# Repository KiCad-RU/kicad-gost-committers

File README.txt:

Build PCAD schematic importer:
# install dependencies
mkdir build
cd build
cmake -DKICAD_SCRIPTING=OFF -DKICAD_SCRIPTING_MODULES=OFF \
      -DKICAD_SCRIPTING_WXPYTHON=OFF \
      -DCMAKE_BUILD_TYPE=Debug \
      -DKICAD_SPICE=OFF \
      -DUSE_PCAD2KICAD=ON \
      -DKICAD_GOST=ON ..
make -j2 pcad2kicadsch
Run:
./extra/pcad2kicadsch/pcad2kicadsch

KiCad README
============
For specific documentation like Compiling, GUI translation, old
changelogs see the Documentation subfolder.

Files
-----
AUTHORS.txt       - The authors, contributors, document writers and translators list
CMakeList.txt     - Main CMAKE build tool script
COPYRIGHT.txt     - A copy of the GNU General Public License Version 2
CTestConfig.cmake - Support for CTest and CDash testing tools
Doxyfile          - Doxygen config file for KiCad
INSTALL.txt       - The release (binary) installation instructions
TODO.txt          - Todo list (looks outdated)
uncrustify.cfg    - Uncrustify config file for uncrustify sources formatting tool

Subdirectories
--------------
3d-viewer         - Sourcecode of the 3D viewer
bitmap2component  - Sourcecode of the bitmap to pcb artwork converter
bitmaps_png       - Menu and program icons
CMakeModules      - Modules for the CMAKE build tool
common            - Sourcecode of the common library
cvpcb             - Sourcecode of the CvPCB tool
demos             - Some demo examples
Documentation     - Developer documentation. Old changelogs etcetera.
eeschema          - Sourcecode of the schematic editor
gerbview          - Sourcecode of the gerber viewer
helpers           - Helper tools and utilities for development
include           - Interfaces to the common library
kicad             - Sourcecode of the project manager
lib_dxf           - Sourcecode of the polygon library
new               - Staging area for the new schematic library format
pagelayout_editor - Sourcecode of the pagelayout editor
patches           - Collection of patches for external dependencies
pcbnew            - Sourcecode of the printed circuit board editor
plugins           - Sourcecode of the new plugin concept
polygon           - Sourcecode of the polygon library
potrace           - Sourcecode of the potrace library
qa                - Testcases using the python interface
resources         - Resources for freedesktop mime-types for linux
scripting         - SWIG Python scripting definitions
scripts           - Helper scripts for various things
template          - Project and pagelayout templates
tools             - Other miscellaneous helpers for testing
utils             - Small utils for kicad, e.g. IDF tools

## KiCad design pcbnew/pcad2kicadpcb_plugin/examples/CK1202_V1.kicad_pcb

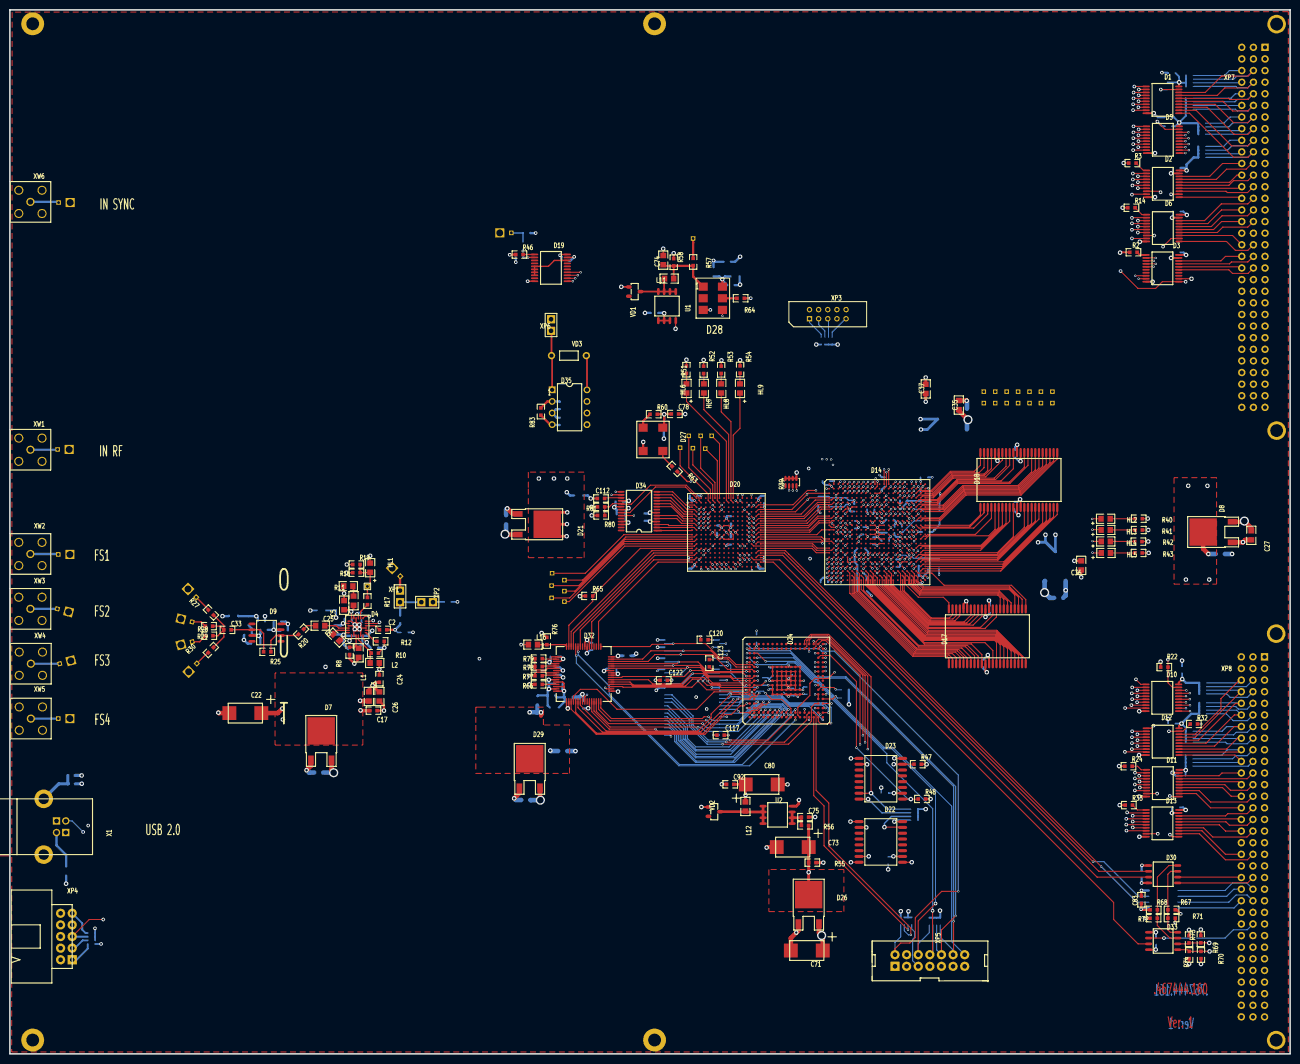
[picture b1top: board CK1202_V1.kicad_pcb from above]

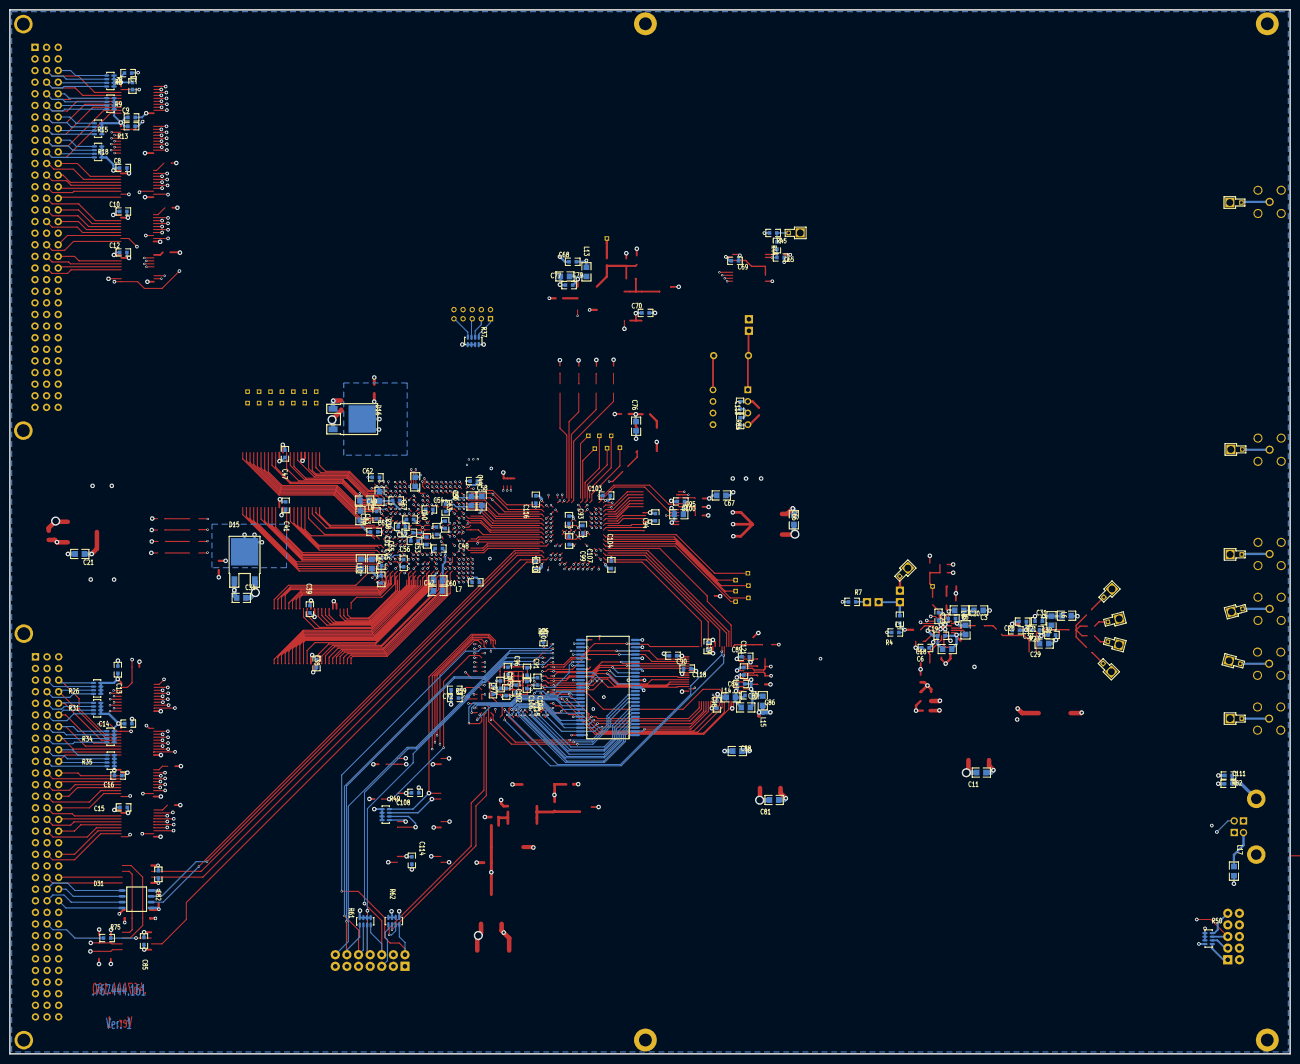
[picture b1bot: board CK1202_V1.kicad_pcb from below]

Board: 6 copper layers, 280.0 x 228.3 mm, 328 parts (151 on the bottom side), 519 nets.

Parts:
1, 2, 4, 5, 6, 7, 8, 9, 10, 11, 12, 13: YESF-085/50; CABLE_1
3: PIN40X40X24; PIN40X40X24_1
C1, C2, C28: 1000; C_SMD0603_1
C3: 0,022 мкФ; C_SMD0805_1
C4: 680; C_SMD0805_1
C5: 47; C_SMD0805_1
C6, C19, C84, C111: 0,01 мк; C_SMD0603_1
C7, C8, C9, C10, C12, C13, C14, C15, C16, C17, C20, C23, C24, C30, C32, C33, C38, C39, C40, C41, C46, C47, C48, C49, C50, C51, C52, C53, C54, C55, C56, C58, C60, C61, C62, C63, C64, C68, C69, C70, C72, C75, C78, C79, C82, C83, C85, C86, C89, C90, C91, C92, C93, C94, C96, C97, C98, C99, C100, C101, C102, C103, C104, C105, C106, C107, C108, C109, C110, C112, C113, C114, C115, C116, C117, C118, C119, C120, C121, C122, C123: 0,1 мк; C_SMD0603_1
C11, C18, C21, C26, C27, C29, C31, C34, C35, C36, C37, C42, C43, C44, C45, C57, C59, C66, C67, C74, C76, C77, C81, C87, C88, C95: 10 мк; C_SMD0805_1
C22, C71, C73, C80: 100; C+7343_1
C25: 100; C_SMD0805_1
C65: 220; C_SMD0603_1
D1, D2, D3, D5, D6, D10, D11, D12, D13, D19: SN74AC245DB; 74AC245_1
D4: ADF4360-8BCP; ADF4360_1
D7, D8, D26: LM1117DTX-3,3; LM1117_1
D9: AD8009AR; AD8009_1
D14: EP2C20F484C7; EP2C20F484_1
D15, D21: LM1117DTX-3,3; LM1117-ADJ_1
D16: LM1117DTX-ADJ; LM1117-ADJ_1
D17, D18: IS61LV51216; IS61LV51216_1_1
D20: EPM1270F256C4; EPM1270F256_1
D22, D23: M25P64V6MF; M25P32_1
D24: ADSP_BF533SBB500; ADSP_BF533_1
D25: MT48LC16M16A2; MT48LC16M16A2_1
D27: KXO-97- 60.000 MHz; KXO-97_1
D28: KXO-75- 10.000 MHz; KXO-75_1
D29: LM1117-2,5; LM1117-ADJ_1
D30, D31: MC100LVEL22D; MC100LVEL22D_1
D32: NET2272; NET2272_1
D33: MC100LVELT23; 100LVELT23_1
D34: FT-245RL; FT-245RL_1
D35: ADM705AN; ADM705_1
HL1, HL3, HL5, HL6, HL8: L-C170 gct; L-C170_1
HL2, HL4, HL7, HL9: L-C170 srct; L-C170_1
L1, L2: 68 нГ; L_SMD0805_1
L3, L6, L7, L8, L9, L10, L11, L12, L13: 10 мкГ; L_SMD0805_1
L4, L5: 56 нГ; L_SMD0805_1
L14, L15: 1 мкГ; L_SMD0805_1
L16, L17: 42 Ом; L_SMD0805_1
R1, R2, R3, R13, R14, R22, R24, R32, R33, R46, R57, R58, R60, R64: 2,2 к; R_SMD0603_1
R4, R7, R27, R28, R29, R30: 51; R_SMD0603_1
R5, R9, R15, R18, R26, R31, R34, R35, R37, R39, R49, R50, R61, R62: 2,2 к; YC164_1
R6: 15 к; R_SMD0805_1
R8, R10: 470; R_SMD0603_1
R11: 6,8 к; R_SMD0805_1
R12, R80: 4,7 к; R_SMD0603_1
R16, R17, R19, R81: 10 к; R_SMD0603_1
R20, R21, R23, R25: 1,2 к; R_SMD0603_1
R36, R44, R45, R59, R63: 100; R_SMD0603_1
R38, R47, R48: 2,2k; R_SMD0603_1
R40, R41, R42, R43, R51, R52, R53, R54: 510; R_SMD0603_1
R55, R56: 0; R_SMD0603_1
R65: 1 к; R_SMD0603_1
R66: 2,43 к; R_SMD0603_1
R67, R68, R69, R70, R79: 1,5 к; R_SMD0603_1
R71, R72, R73, R74: 820; R_SMD0603_1
R75: 33; R_SMD0603_1
R76: 47 к; R_SMD0603_1
R77, R78: 39,2; R_SMD0603_1
R82: 1 М; R_SMD0603_1
R83, R84: 2,2K; R_SMD0603_1
TP1, TP2, TP3, TP4, TP5, TP6, TP7, TP8, TP9, TP10, TP11, TP12, TP13, TP14, TP15, TP16, TP17, TP18, TP19, TP20, TP21, TP22, TP23, TP24, TP25, TP26, TP27: PIN40X40X24; PIN40X40X24_1
U1, U2: FDS9431A; NDS8434A_1
VD1, VD2: ZHCS1000; ZHCS1000_1
VD3: 2D522B; 2D522B_1
X1: URB-1001; USB_1
XP1, XP2, XP6: XP-JP; XP-JP_1
XP3: BH2-10; BH2-10_1
XP4: BH10R; BH10R_1
XP5: BH-14; BH14_1
XP7, XP8: DIN EN 60603 121 A 10139 X; DIN3X32P_1
XW1, XW2, XW3, XW4, XW5, XW6: C340-022D; SMB_JWHY_1

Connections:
1S: D3.11, D19.14, D20.A12, XP7.C29
1_CW: D6.11, XP7.B18
1_DIR1: D1.1, D14.A3
1_IO0: D1.2, D14.A4
1_IO1: D1.3, D14.B4
1_IO2: D1.4, D14.C4
1_IO3: D1.5, D14.A5
1_IO4: D1.6, D14.B5
1_IO5: D1.7, D14.A6
1_IO6: D1.8, D14.B6
1_IO7: D1.9, D14.A7
1_OUT0: D1.18, R5.2, XP7.B3
1_OUT1: D1.17, R5.4, XP7.B4
1_OUT2: D1.16, R9.2, XP7.B5
1_OUT3: D1.15, R9.4, XP7.B6
1_OUT4: D1.14, R15.2, XP7.B7
1_OUT5: D1.13, R15.4, XP7.B8
1_OUT6: D1.12, R18.2, XP7.B9
1_OUT7: D1.11, R18.4, XP7.B10
1_P_A0: D2.15, XP7.B12
1_P_A1: D2.13, XP7.B13
1_P_A2: D6.18, XP7.B14
1_P_CW: D6.9, D14.A19
1_P_RDY: D6.6, D14.C17
1_P_RQ: D6.12, D14.B20
1_P_R\W: D6.4, D14.A17
1_RDY: D6.14, XP7.B16
1_RQ: D6.8, XP7.B17
1_R\W: D6.16, XP7.B15
1_STROB: D2.17, XP7.B11
1_STR_0: D2.3, D14.B13
1__A0: D2.5, D14.B14
1__A1: D2.7, D14.B15
1__A2: D6.2, D14.B16
1_~OE1: D1.19, D14.B3, R1.B
2S: D19.13, D20.B12
2_CW: D6.13, XP7.C18
2_DIR1: D5.1, D14.C7
2_IO0: D5.2, D14.A8
2_IO1: D5.3, D14.B8
2_IO2: D5.4, D14.A9
2_IO3: D5.5, D14.B9
2_IO4: D5.6, D14.C9
2_IO5: D5.7, D14.A10
2_IO6: D5.8, D14.B10
2_IO7: D5.9, D14.A11
2_OUT0: D5.18, R5.1, XP7.C3
2_OUT1: D5.17, R5.3, XP7.C4
2_OUT2: D5.16, R9.1, XP7.C5
2_OUT3: D5.15, R9.3, XP7.C6
2_OUT4: D5.14, R15.1, XP7.C7
2_OUT5: D5.13, R15.3, XP7.C8
2_OUT6: D5.12, R18.1, XP7.C9
2_OUT7: D5.11, R18.3, XP7.C10
2_P_A0: D2.16, XP7.C12
2_P_A1: D2.14, XP7.C13
2_P_A2: D2.11, XP7.C14
2_P_CW: D6.7, D14.C18
2_P_RDY: D6.5, D14.B17
2_P_RQ: D2.12, D14.A20
2_P_R\W: D6.3, D14.C16
2_RDY: D6.15, XP7.C16
2_RQ: D2.8, XP7.C17
2_R\W: D6.17, XP7.C15
2_STROB: D2.18, XP7.C11
2_STR_0: D2.2, D14.A13
2__A0: D2.4, D14.A14
2__A1: D2.6, D14.A15
2__A2: D2.9, D14.A16
2_~OE1: D5.19, D14.B7, R13.B
3S: D19.12, D20.A11
3_CW: D13.12, XP8.B18
3_DIR1: D10.1, D14.P15
3_IO0: D10.2, D14.U2
3_IO1: D10.3, D14.U3
3_IO2: D10.4, D14.V2
3_IO3: D10.5, D14.W3
3_IO4: D10.6, D14.Y4
3_IO5: D10.7, D14.Y3
3_IO6: D10.8, D14.AA4
3_IO7: D10.9, D14.AB4
3_OUT0: D10.18, R26.2, XP8.B3
3_OUT1: D10.17, R26.4, XP8.B4
3_OUT2: D10.16, R31.2, XP8.B5
3_OUT3: D10.15, R31.4, XP8.B6
3_OUT4: D10.14, R34.2, XP8.B7
3_OUT5: D10.13, R34.4, XP8.B8
3_OUT6: D10.12, R35.2, XP8.B9
3_OUT7: D10.11, R35.4, XP8.B10
3_P_A0: D11.15, XP8.B12
3_P_A1: D11.13, XP8.B13
3_P_A2: D13.18, XP8.B14
3_P_CW1: D13.8, D14.M19
3_P_RDY: D13.6, D14.L19
3_P_RQ: D11.11, D14.P17
3_P_R\W: D13.4, D14.J18
3_RDY: D13.14, XP8.B16
3_RQ: D11.9, XP8.B17
3_R\W: D13.16, XP8.B15
3_STROB: D11.17, XP8.B11
3_STR_0: D11.3, D14.D15
3__A0: D11.5, D14.E19
3__A1: D11.7, D14.G18
3__A2: D13.2, D14.H19
3_~OE1: D10.19, D14.N15, R22.B
4S: D19.11, D20.B11
4_CW: D13.13, XP8.C18
4_DIR1: D12.1, D14.R18
4_IO0: D12.2, D14.AA3
4_IO1: D12.3, D14.AB3
4_IO2: D12.4, D14.Y2
4_IO3: D12.5, D14.Y1
4_IO4: D12.6, D14.W2
4_IO5: D12.7, D14.W1
4_IO6: D12.8, D14.V1
4_IO7: D12.9, D14.U1
4_OUT0: D12.18, R26.1, XP8.C3
4_OUT1: D12.17, R26.3, XP8.C4
4_OUT2: D12.16, R31.1, XP8.C5
4_OUT3: D12.15, R31.3, XP8.C6
4_OUT4: D12.14, R34.1, XP8.C7
4_OUT5: D12.13, R34.3, XP8.C8
4_OUT6: D12.12, R35.1, XP8.C9
4_OUT7: D12.11, R35.3, XP8.C10
4_P_A0: D11.16, XP8.C12
4_P_A1: D11.14, XP8.C13
4_P_A2: D11.12, XP8.C14
4_P_CW1: D13.7, D14.L18
4_P_RDY: D13.5, D14.J17
4_P_RQ: D13.11, D14.R19
4_P_R\W: D13.3, D14.H18
4_RDY: D13.15, XP8.C16
4_RQ: D13.9, XP8.C17
4_R\W: D13.17, XP8.C15
4_STROB: D11.18, XP8.C11
4_STR_0: D11.2, D14.D14
4__A0: D11.4, D14.E18
4__A1: D11.6, D14.F15
4__A2: D11.8, D14.G17
4_~OE1: D12.19, D14.P18, R32.B
7DATA0: D14.K4, D20.C15
7MSEL0: D14.M17, R38.A
7MSEL1: D14.N17, R36.A
7NCONF: D14.L4, D20.C13, R39.2
7VPLL1: C42.A, C48.A, D14.U7, L7.A
7VPLL2: C43.A, C49.A, D14.F16, L8.A
7VPLL3: C44.A, C50.A, D14.E6, L9.A
7VPLL4: C45.A, C51.A, D14.U16, L10.A
10M: D3.12, XP7.B29
10MHZ: D20.D7, D28.4
20MHZ: D20.D5, R7.B
30MHZ: D20.C3, D32.25
60MHZ: D20.J5, R63.B
+1,2V7: C37.A, C40.A, C46.A, C53.A, C55.A, C56.A, C59.A, D14.E5, D14.F17, D14.J10, D14.J11, D14.J12, D14.J13, D14.K9, D14.K14, D14.L9, D14.L14, D14.M9, D14.M14, D14.N9, D14.N14, D14.P10, D14.P11, D14.P12, D14.P13, D14.U6, D14.U17, D16.2, L7.B, L8.B, L9.B, L10.B
+2,5V: C88.A, C89.A, C90.A, D29.2, D32.1, D32.3, D32.48, L15.A
+3,3V: C20.A, C23.A, C24.A, C26.A, D4.2, D4.21, D4.23, L3.B, L4.A, R16.B
+3,3V2: C7.B, C8.A, C9.A, C10.A, C12.A, C13.A, C14.A, C15.A, C16.A, C21.A, D1.20, D2.20, D3.20, D5.20, D6.20, D8.2, D10.20, D11.20, D12.20, D13.20, R1.A, R2.A, R3.A, R5.5, R5.6, R5.7, R5.8, R9.5, R9.6, R9.7, R9.8, R13.A, R14.A, R15.5, R15.6, R15.7, R15.8, R18.5, R18.6, R18.7, R18.8, R22.A, R24.A, R26.5, R26.6, R26.7, R26.8, R31.5, R31.6, R31.7, R31.8, R32.A, R33.A, R34.5, R34.6, R34.7, R34.8, R35.5, R35.6, R35.7, R35.8
+3,3V7: C36.A, C38.A, C39.A, C41.A, C47.A, C52.A, C54.A, C57.A, C58.B, C60.B, C61.A, C62.B, C63.A, C64.B, D14.A2, D14.A21, D14.AA1, D14.AA22, D14.AB2, D14.AB21, D14.B1, D14.B22, D14.C6, D14.C11, D14.C12, D14.D17, D14.E10, D14.E13, D14.G9, D14.G14, D14.G19, D14.J7, D14.J16, D14.L3, D14.L20, D14.M3, D14.M20, D14.P7, D14.P16, D14.T4, D14.T9, D14.T14, D14.T19, D14.V10, D14.V13, D14.W6, D14.W17, D14.Y11, D14.Y12, D15.2, D17.11, D17.33, D18.11, D18.33, R37.5, R37.6, R37.7, R38.B, R39.5, R39.6, R39.7, R39.8, XP3.P4
+3,3VF: C67.A, C68.B, C69.A, C70.A, C82.A, C83.B, C85.A, C93.A, C94.A, C98.A, C99.A, C103.A, C104.A, C107.A, C110.A, C116.A, C118.A, C119.A, C121.A, D19.20, D20.A3, D20.A14, D20.C1, D20.C16, D20.F8, D20.F9, D20.H6, D20.H8, D20.H10, D20.H11, D20.J6, D20.J7, D20.J9, D20.J11, D20.L8, D20.L9, D20.P1, D20.P16, D20.T3, D20.T14, D21.2, D30.8, D31.8, D32.7, D32.27, D32.42, D32.55, D33.8, D34.4, L13.A, R46.B, R47.B, R48.B, R49.5, R49.6, R49.7, R49.8, R64.B, R65.A, R71.B, R72.B, R73.A, R74.A, R80.A, U1.1, U1.2, U1.3
+5V: C11.A, C27.A, C31.A, C32.A, C34.A, C35.A, C66.A, C71.1, C76.A, C78.A, C81.A, C95.A, C100.A, C113.A, D7.3, D8.3, D15.3, D16.3, D21.3, D26.3, D27.4, D29.3, D34.20, D35.2, L6.A, R50.5, R50.6, R50.7, R60.B, R83.A, XP4.P4, XP8.A29, XP8.A30, XP8.B29, XP8.B30, XP8.C29, XP8.C30
A0: D14.U13, D20.P13, D24.J16, D25.23, D32.32
A1: D14.V11, D20.N13, D24.J17, D25.24, D32.31
A2: D14.T11, D20.N12, D24.K16, D25.25, D32.30
A3: D14.T12, D20.P12, D24.K17, D25.26, D32.29
A4: D14.W9, D20.N11, D24.L16, D25.29, D32.28
A5: D14.U10, D20.P11, D24.L17, D25.30
A6: D14.U9, D20.R11, D24.M16, D25.31
A7: D14.V9, D20.R10, D24.M17, D25.32
A8: D14.U8, D24.N17, D25.33
A9: D14.T8, D24.N16, D25.34
A10: D14.W7, D24.P17
A11: D14.W4, D24.P16, D25.35
A12: D14.V4, D24.R17, D25.36
A13: D14.T3, D24.R16
A14: D14.H4, D24.T17
A15: D14.G5, D24.U15
A16: D14.U4, D20.T10, D24.T15
A17: D14.W5, D20.T5, D24.U16, D25.20
A18: D14.J4, D20.R8, D24.T14, D25.21
AA0: D14.Y5, D17.1
AA1: D14.AB6, D17.2
AA2: D14.AA6, D17.3
AA3: D14.Y6, D17.4
AA4: D14.AB7, D17.5
AA5: D14.AB11, D17.18
AA6: D14.AA11, D17.19
AA7: D14.AB12, D17.20
AA8: D14.AA12, D17.21
AA9: D14.AB13, D17.22
AA10: D14.Y20, D17.23
AA11: D14.AA20, D17.24
AA12: D14.AB20, D17.25
AA13: D14.Y19, D17.26
AA14: D14.AA19, D17.27
AA15: D14.AB17, D17.42
AA16: D14.AA17, D17.43
AA17: D14.Y17, D17.44
AA18: D14.AB19, D17.28
AB0: D14.K22, D18.1
AB1: D14.K21, D18.2
AB2: D14.K20, D18.3
AB3: D14.N21, D18.4
AB4: D14.N22, D18.5
AB5: D14.V22, D18.18
AB6: D14.W21, D18.19
AB7: D14.W22, D18.20
AB8: D14.Y21, D18.21
AB9: D14.Y22, D18.22
AB10: D14.J22, D18.23
AB11: D14.J21, D18.24
AB12: D14.J20, D18.25
AB13: D14.G22, D18.26
AB14: D14.G21, D18.27
AB15: D14.C22, D18.42
AB16: D14.C21, D18.43
AB17: D14.C20, D18.44
AB18: D14.G20, D18.28
ACE: D14.AA7, D17.6
ALE: D20.P2, D32.53
AOE: D14.Y16, D17.41
AVSS: C84.B, C86.B, C87.B, D32.12, D32.14, D32.16, L14.B
AWE: D14.Y10, D17.17
BCE: D14.R20, D18.6
BF_TCK: D24.U4, R61.7, XP5.P8
BF_TDI: D24.U3, R61.5, XP5.P12
BF_TDO: D24.T4, XP5.P14
BF_TMS: D24.T3, R61.8, XP5.P6
BF_TRS: D24.U2, R61.6, XP5.P10
BLOK: D3.15, XP7.B20
BMOD0: D20.T8, D24.U5
BMOD1: D20.T9, D24.T5
BOE: D14.D20, D18.41
BWE: D14.V21, D18.17
CKP: D20.N16, D31.7
CLKF: D14.L1, D14.L2, D20.J16
CLKIN: D20.E14, D24.A14
CLKOUT: D24.D16, D25.38
CLK_ADF: D4.17, D20.G5
CLK_N: D31.2, XP8.C21
CLK_P: D31.1, XP8.B21
CONFD7: D14.N18, D20.C14, R39.3
D0: D14.D3, D20.T7, D24.U14, D25.2, D32.19
D1: D14.H3, D20.R7, D24.T12, D25.4, D32.20
D2: D14.P5, D20.R6, D24.U13, D25.5, D32.21
D3: D14.P3, D20.T6, D24.T11, D25.7, D32.22
D4: D14.C3, D20.R5, D24.U12, D25.8, D32.23
D5: D14.D4, D20.M3, D24.U11, D25.10, D32.35
D6: D14.T5, D20.M4, D24.T10, D25.11, D32.36
D7: D14.E3, D20.T4, D24.U10, D25.13, D32.37
D8: D14.N4, D20.G4, D24.T9, D25.42, D32.38
D9: D14.E4, D20.G3, D24.U9, D25.44, D32.39
D10: D14.N3, D20.F4, D24.T8, D25.45, D32.43
D11: D14.F3, D20.D3, D24.U8, D25.47, D32.44
D12: D14.F4, D20.E3, D24.U7, D25.48, D32.45
D13: D14.M6, D20.E4, D24.T7, D25.50, D32.46
D14: D14.G3, D20.F3, D24.U6, D25.51, D32.47
D15: D14.M5, D20.D4, D24.T6, D25.53, D32.49
DA0: D14.Y7, D17.7
DA1: D14.AB8, D17.8
DA2: D14.AA8, D17.9
DA3: D14.AB9, D17.10
DA4: D14.AA9, D17.13
DA5: D14.Y9, D17.14
DA6: D14.AB10, D17.15
DA7: D14.AA10, D17.16
DA8: D14.Y18, D17.29
DA9: D14.AA18, D17.30
DA10: D14.AA13, D17.31
DA11: D14.Y13, D17.32
DA12: D14.AB14, D17.35
DA13: D14.AA14, D17.36
DA14: D14.Y14, D17.37
DA15: D14.AB15, D17.38
DB0: D14.R21, D18.7
DB1: D14.R22, D18.8
DB2: D14.T21, D18.9
DB3: D14.T22, D18.10
DB4: D14.U20, D18.13
DB5: D14.U21, D18.14
DB6: D14.U22, D18.15
DB7: D14.V20, D18.16
DB8: D14.F22, D18.29
DB9: D14.F21, D18.30
DB10: D14.F20, D18.31
DB11: D14.E22, D18.32
DB12: D14.E21, D18.35
DB13: D14.E20, D18.36
DB14: D14.D22, D18.37
DB15: D14.D21, D18.38
DCLK7: D14.L6, D20.L15
DP: D20.P14, D30.7
DREQ: D20.M2, D32.62
DT_N: D30.2, XP8.C20
DT_P: D30.1, XP8.B20
DU0: D20.H1, D34.1
DU1: D20.G2, D34.5
DU2: D20.G1, D34.3
DU3: D20.E2, D34.11
DU4: D20.H2, D34.2
DU5: D20.F2, D34.9
DU6: D20.E1, D34.10
DU7: D20.F1, D34.6
D_ADF: D4.18, D20.F5
D_I: D20.R16, D33.7
D_IN: D33.1, R70.B, R74.B, XP8.B23
GND: 1.GND, 2.GND, 4.GND, 5.GND, 6.GND, 7.GND, 8.GND, 9.GND, 10.GND, 11.GND, 12.GND, 13.GND, C3.A, C5.A, C6.A, C7.A, C8.B, C9.B, C10.B, C11.B, C12.B, C13.B, C14.B, C15.B, C16.B, C17.B, C20.B, C21.B, C22.2, C23.B, C24.B, C26.B, C27.B, C28.B, C29.B, C30.B, C31.B, C32.B, C34.B, C35.B, C36.B, C37.B, C38.B, C39.B, C40.B, C41.B, C42.B, C43.B, C44.B, C45.B, C46.B, C47.B, C48.B, C49.B, C50.B, C51.B, C52.B, C53.B, C54.B, C55.B, C56.B, C57.B, C58.A, C59.B, C60.A, C61.B, C62.A, C63.B, C64.A, C65.B, C66.B, C67.B, C68.A, C69.B, C70.B, C71.2, C72.B, C73.2, C74.B, C75.B, C76.B, C77.B, C78.B, C79.B, C80.2, C81.B, C82.B, C83.A, C85.B, C88.B, C89.B, C90.B, C91.B, C92.B, C93.B, C94.B, C95.B, C96.B, C97.B, C98.B, C99.B, C100.B, C101.B, C102.B, C103.B, C104.B, C105.B, C106.B, C107.B, C108.B, C109.B, C110.B, C111.B, C112.B, C113.B, C114.B, C115.B, C116.B, C117.B, C118.B, C119.B, C120.B, C121.B, C122.B, C123.B, D1.10, D2.10, D2.19, D3.10, D3.19, D4.1, D4.3, D4.8, D4.11, D4.15, D4.22, D4.25, D5.10, D6.10, D6.19, D7.1, D8.1, D9.4, D10.10, D11.10, D11.19, D12.10, D13.10, D13.19, D14.A1, D14.A22, D14.AA2, D14.AA21, D14.AB1, D14.AB22, D14.B2, D14.B21, D14.C5, D14.C8, D14.C15, D14.D10, D14.D13, D14.D18, D14.E16, D14.E17, D14.F5, D14.F6, D14.F7, D14.F18, D14.F19, D14.G4, D14.G10, D14.G13, D14.H20, D14.K1, D14.K3, D14.K7, D14.K10, D14.K11, D14.K12, D14.K13, D14.K16, D14.K19, D14.L10, D14.L11, D14.L12, D14.L13, D14.M4, D14.M10, D14.M11, D14.M12, D14.M13, D14.N7, D14.N10, D14.N11, D14.N12, D14.N13, D14.N16, D14.N19, D14.R3, D14.T10, D14.T13, D14.T17, D14.T20, D14.U5, D14.V3, D14.V5, D14.V6, D14.V7, D14.V16, D14.V17, D14.V18, D14.W10, D14.W13, D14.W19, D14.Y8, D14.Y15, D15.1, D16.1, D17.12, D17.34, D17.39, D17.40, D18.12, D18.34, D18.39, D18.40, D19.10, D19.19, D20.A1, D20.A16, D20.B2, D20.B15, D20.G7, D20.G8, D20.G9, D20.G10, D20.H7, D20.H9, D20.J8, D20.J10, D20.K7, D20.K8, D20.K9, D20.K10, D20.R2, D20.R15, D20.T1, D20.T16, D21.1, D22.10, D23.10, D24.B16, D24.F11, D24.G7, D24.G8, D24.G9, D24.G10, D24.G11, D24.H7, D24.H8, D24.H9, D24.H10, D24.H11, D24.J7, D24.J8, D24.J9, D24.J10, D24.J11, D24.K7, D24.K8, D24.K9, D24.K10, D24.K11, D24.L7, D24.L8, D24.L9, D24.L10, D24.L11, D24.M9, D24.T16, D25.6, D25.12, D25.28, D25.41, D25.46, D25.52, D25.54, D26.1, D27.2, D28.3, D29.1, D30.5, D31.5, D32.4, D32.10, D32.17, D32.18, D32.24, D32.33, D32.40, D32.41, D32.54, D32.56, D33.5, D34.7, D34.18, D34.21, D34.25, D34.26, D35.3, HL1.2, L1.B, L2.B, L14.A, L17.B, R4.A, R8.B, R10.B, R11.B, R12.A, R19.B, R21.B, R36.B, R37.8, R40.B, R41.B, R42.B, R43.B, R45.B, R50.8, R51.B, R52.B, R53.B, R54.B, R58.A, R59.A, R62.1, R66.A, R67.A, R68.A, R69.A, R70.A, R76.B, R81.A, R82.B, R84.A, VD1.3, VD2.3, XP3.P2, XP3.P10, XP4.P2, XP4.P10, XP5.P1, XP5.P4, XP5.P7, XP5.P9, XP5.P11, XP5.P13, XP6.2, XP7.A1, XP7.A2, XP7.A31, XP7.A32, XP7.B1, XP7.B2, XP7.B31, XP7.B32, XP7.C1, XP7.C2, XP7.C31, XP7.C32, XP8.A1, XP8.A2, XP8.A31, XP8.A32, XP8.B1, XP8.B2, XP8.B31, XP8.B32, XP8.C1, XP8.C2, XP8.C31, XP8.C32, XW1.2, XW1.3, XW1.4, XW1.5, XW2.2, XW2.3, XW2.4, XW2.5, XW3.2, XW3.3, XW3.4, XW3.5, XW4.2, XW4.3, XW4.4, XW4.5, XW5.2, XW5.3, XW5.4, XW5.5, XW6.2, XW6.3, XW6.4, XW6.5
H0: D14.R1, D20.L16
H1: D14.T1, D20.M16
H2: D14.R2, D20.L14
H3: D14.E1, D20.E16
H4: D14.D2, D20.E15
H5: D14.F1, D20.F16
H6: D14.E2, D20.F15
H7: D14.H1, D20.G16
H8: D14.F2, D20.G15
H9: D14.J1, D20.H16
H10: D14.H2, D20.H15
H11: D14.J2, D20.J15
H12: D14.N1, D20.K15
H13: D14.P2, D20.K16
INT_USB: D20.M1, D32.63, R65.B
I_1S: D3.9, D14.D1, D20.D16
I_10M: D3.8, D14.C1, D20.D15
LE_ADF: D4.19, D20.E5
MAX-TCK: D20.P3, R50.1, XP4.P1
MAX-TDI: D20.L6, R50.4, XP4.P9
MAX-TDO: D20.M5, R50.2, XP4.P3
MAX-TMS: D20.N4, R50.3, XP4.P5
MISO: D22.8, D23.8, D24.E2, R49.1
MOSI: D22.15, D23.15, D24.E1, R49.4
NET00000: D28.5, R64.A
NET00001: 12.RF, R44.A, R45.A
NET00002: C112.A, D34.17
NET00003: C65.A, D19.2, R44.B
NET00004: C25.A, D4.4
NET00006: D19.5, D19.6, D19.7, D19.8, D19.18
NET00007: D4.5, L5.A
NET00008: 7.RF, R30.B
NET00009: 6.RF, R29.B
NET00010: 9.RF, XW3.1
NET00011: 8.RF, XW2.1
NET00012: 1.RF, XW1.1
NET00013: 2.RF, XP1.1
NET00014: D4.20, R17.A
NET00015: 3.1, HL1.1, R16.A, R17.B, R19.A
NET00016: L17.A, X1.4
NET00019: C18.B, C19.B, D4.6, L4.B, L5.B
NET00020: 13.RF, XW6.1
NET00022: C25.B, R20.A
NET00026: C18.A, C19.A, D4.14
NET00027: C4.B, C5.B, D4.24, R6.B
NET00028: C3.B, D4.7, R6.A
NET00029: C4.A, R11.A
NET00031: D4.13, R12.B
NET00032: C6.B, D4.12
NET00033: D4.9, L1.A, R8.A
NET00034: D4.10, L2.A, R10.A
NET00039: C2.B, D4.16
NET00040: C1.B, C2.A, R4.B
NET00042: C111.A, R82.A, X1.5, X1.6
NET00140: 4.RF, R27.B
NET00142: 5.RF, R28.B
NET00143: D11.1, R24.B
NET00144: 10.RF, XW4.1
NET00145: D3.1, R2.B
NET00146: 11.RF, XW5.1
NET00147: C33.B, R27.A, R28.A, R29.A, R30.A
NET00148: D13.1, R33.B
NET00152: C29.A, C30.A, D9.7, L6.B, R23.B
NET00158: C17.A, C22.1, D7.2, L3.A
NET00210: HL9.2, R54.A
NET00214: HL7.2, R52.A
NET00215: HL6.2, R51.A
NET00216: HL8.2, R53.A
NET00255: C73.1, D26.2, R55.B, R56.A
NET00256: L16.A, X1.1
NET00264: C77.A, C79.A, D28.6, L13.B
NET00265: L11.B, U1.5, U1.6, U1.7, U1.8, VD1.1
NET00266: C74.A, D28.1, L11.A, R57.B, R58.B
NET00268: D27.3, R63.A
NET00271: L12.B, U2.5, U2.6, U2.7, U2.8, VD2.1
NET00308: D27.1, R60.A
NET00312: C75.A, R56.B, U2.1, U2.2, U2.3
NET00350: D35.4, R83.B, R84.B
NET00352: D35.1, VD3.1, XP6.1
NET00353: D35.8, VD3.2
NET00375: D19.1, R46.A
NET00384: C1.A, XP1.2, XP2.1
NET00385: R7.A, XP2.2
NET00401: HL2.2, R40.A
NET00402: HL3.2, R41.A
NET00403: HL4.2, R42.A
NET00404: HL5.2, R43.A
NET00541: C28.A, D9.3, R21.A, R23.A
NET00542: D9.2, R20.B, R25.A
NET00544: C33.A, D9.6, R25.B
NET001490: D6.1, R14.B
NET001500: D2.1, R3.B
NSTAT7: D14.N20, R39.4
OUT: C72.A, D24.A13
PF0: D20.H13, D24.D2
PF1: D20.G13, D24.C1
PF2: D22.7, D24.B1, R49.2
PF3: D23.7, D24.C2, R47.A
PF4: D14.V15, D24.A1
PF5: D14.W15, D24.A2
PF6: D20.H14, D24.B3
PF7: D14.T16, D24.A3
PF8: D22.1, D23.1, D24.B4, R48.A
PF9: D14.U18, D20.F13, D24.A4
PF10: D20.J14, D24.B5
PF11: D14.T18, D20.F14, D24.A5
PF12: D20.E13, D24.A6
PF13: D20.J13, D24.B6
PF14: D14.V19, D24.A7
PF15: D14.U19, D24.B7
PPI: D20.K14, D24.B10
PUSK: D3.17, XP7.B19
PVDD: C84.A, C86.A, C87.A, D32.11, D32.15, L15.B
PWR: D20.D1, D34.12
P_BLOK: D3.5, D14.H13
P_PUSK: D3.3, D14.H15
P_RES: D3.2, D14.H16
R5: D24.C16, R62.7
R6: D24.C17, R62.6
R7: D24.B11, R59.B
R8: R62.5, XP5.P5
RD_U: D20.D2, D34.13
RPU: D32.2, R79.A
RREF: D32.13, R66.B
RS: D30.3, D33.4, R67.B, R71.A
RSDM: D32.9, R77.A
RSDP: D32.5, R78.A
RSR: D33.6, R75.A
RSS: R75.B, XP8.B24
RS_I: D20.C6, D35.7
RU: D20.B3, D34.19, R80.B, R81.B
RXF: D20.B1, D34.23
SA10: D24.B15, D25.22
SCK: D22.16, D23.16, D24.D1, R49.3
SCKE: D24.B14, D25.37
SHIM: D20.C7, U1.4
STP: D20.N15, D31.6
STR_N: D31.4, XP8.C22
STR_P: D31.3, XP8.B22
TCK7: D14.K2, R37.1, XP3.P1
TDI7: D14.K5, R37.4, XP3.P9
TDO7: D14.L5, R37.2, XP3.P3
TMS7: D14.K6, R37.3, XP3.P5
TP1: D14.E8, TP1.1
TP2: D14.B11, TP2.1
TP3: D14.F10, TP3.1
TP4: D14.D11, TP4.1
TP5: D14.F12, TP5.1
TP6: D14.D16, TP6.1
TP7: D14.C19, TP7.1
TP8: D14.F8, TP8.1
TP9: D14.F9, TP9.1
TP10: D14.E11, TP10.1
TP11: D14.F11, TP11.1
TP12: D14.F13, TP12.1
TP13: D14.B19, TP13.1
TP14: D14.D19, TP14.1
TP15: D20.A5, TP15.1
TP16: D20.A6, TP16.1
TP17: D20.A7, TP17.1
TP18: D20.B5, TP18.1
TP19: D20.B6, TP19.1
TP20: D20.B7, TP20.1
TP21: D20.J1, TP21.1
TP22: D20.J2, TP22.1
TP23: D20.K1, TP23.1
TP24: D20.K2, TP24.1
TP25: D20.L1, TP25.1
TP26: D20.L2, TP26.1
TP27: R57.A, TP27.1
TXE: D20.A2, D34.22
USB+: D34.15, XP4.P6
USB-: D34.16, XP4.P8
USB_DM: D32.8, R77.B, X1.2
USB_DP: D32.6, R78.B, R79.B, X1.3
VBUS: D32.64, L16.B, R76.A
VD1: D20.B9, HL6.1
VD2: D20.A9, HL7.1
VD3: D20.B10, HL8.1
VD4: D20.A10, HL9.1
VD5: D14.G12, HL2.1
VD6: D14.G11, HL3.1
VD7: D14.H12, HL4.1
VD8: D14.H11, HL5.1
VDDEXT: C91.A, C96.A, C101.A, C105.A, C108.A, C114.A, C117.A, C120.A, C122.A, C123.A, D22.2, D23.2, D24.B2, D24.F6, D24.F7, D24.F8, D24.F9, D24.F10, D24.G6, D24.H6, D24.J6, D24.K6, D24.L6, D24.M6, D24.M7, D24.M8, D24.T2, D25.1, D25.3, D25.9, D25.14, D25.27, D25.43, D25.49, R55.A, R61.1, R61.2, R61.3, R61.4, R62.2, R62.3, R62.4
VDDINT: C80.1, C92.A, C97.A, C102.A, C106.A, C109.A, C115.A, D24.F12, D24.G12, D24.H12, D24.J12, D24.K12, D24.L12, D24.M10, D24.M11, D24.M12, L12.A
VROUT: D24.B12, D24.B13, U2.4
W/VP: D20.D12, D22.9, D23.9
WR_U: D20.C2, D34.14
_RSS: D20.P15, D30.6
~ABE0: D24.H16, D25.15
~ABE1: D24.H17, D25.39
~AMS0: D20.K13, D24.D17
~AMS1: D14.U15, D24.E16
~AOE: D14.W20, D20.D13, D24.F17
~ARE: D14.W11, D20.L12, D24.G16, D32.59
~AWE: D14.U14, D20.L11, D24.G17, D32.60
~DMA_RD: D20.R1, D32.50
~DMA_WR: D20.C4, D32.34
~DRES: D20.G14, D24.A12
~D_IN: D33.2, R69.B, R73.B, XP8.C23
~EMU: D24.U1, R62.8, XP5.P2
~P_ZAP: D3.4, D14.H14
~RESET: D3.18, XP7.C19
~RS: D30.4, D33.3, R68.B, R72.A
~RSUSB: D20.N2, D32.58
~SCAS: D24.A16, D25.17
~SMS: D24.A17, D25.19
~SRAS: D24.A15, D25.18
~SWE: D24.B17, D25.16
~USB: D20.N1, D32.61
~WDI: D20.D6, D35.6
~ZAP: D3.16, XP7.C20

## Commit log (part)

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2016-01-29 pcbnew: support for removing NETINFO_ITEMS from BOARD for proper netlist undo
2016-01-29 One-click PCB update improvements - Fix repetitive undo/redo segfaults & assertions. - Add Update menu entry on PCB side. - Fix Python build error - Add spread footprints after updating
2016-01-31 Improved 3D cache manager's ability to replace outdated cache models
2016-02-01 Remove accidental activation of SG->VRML debug write
2016-02-01 pcbnew: avoid unnecessary copy in RN_NET::processPads()
    Saves >30% run time on ratsnest rebuild for high-fanout nets.
2016-02-02 Forced smoothed normals calculations for VMRML2 parser
2016-02-03 Fixed VRML normals calculations
2016-02-04 Documentation: add version 5 road map to developer documentation.
2016-02-04 github fix and comment improvements: * Fix a StrPrintf() %s count mismatch bug * Better comments * Use std::string::data() instead of a ref to the first char to get the str::string buffer (should not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
2016-02-05 Eeschema: move find sheet by name from SCH_SHEET_PATH to SCH_SHEET.
    * Move FindSheetByName() function from SCH_SHEEET_PATH to SCH_SHEET object
    and update calls to FindSheetByName() accordingly.
    * Remove SCH_SHEET_PATH::FindSheet() which was unused.
    * Add sorting option to SCH_SHEET::GetSheets().
2016-02-06 Removed temporary debug info message
2016-02-07 Eeschema: fix annotation bugs. (fixes lp:1542579)
    * Ensure proper SCH_SHEET object page numbering which caused annotation to
    calculate incorrect reference designators when annotating by using page offsets.
    * Added SetPageNumbers to SCH_SHEET for setting sheet page numbers after
    schematic is loaded.
2016-02-08 Fix minor Bug #1542935 (No solder mask unless there is something on the layer)
2016-02-09 Set the courtyard width to 0.05mm to comply with KLC in the following python footprint generators: bga,qfp,sdip and zip
2016-02-11 fix Tickness typo
2016-02-11 Fixed coloring bugs related to uninitialized variable
2016-02-12 Fixed bug: X3D models not scaled to conform to legacy expectation
2016-02-14 Python footprint generators: fix a typo and fix text size (accordance KLC 6.9)
2016-02-15 Eeschema: Files menu: better name and better comment for the Import sheet content from a project in the current sheep command.
2016-02-15 FindwxWidgets.cmake: Use uppercase for DBG_MSG macro
2016-02-15 FindwxWidgets.cmake: documentation for variables
2016-02-15 FindwxWidgets.cmake: Fix indentation
2016-02-15 FindwxWidgets.cmake: Determine version even when not asked to
2016-02-15 FindwxWidgets.cmake: Reformat documentation
2016-02-15 FindwxWidgets.cmake: Add comment describing code block
2016-02-15 Undo commit -r 6539
2016-02-15 Undo commit -r6509.
2016-02-15 Undo commit -r 6457.
2016-02-15 Undo commit -r 6380.
2016-02-15 Merged Mario's fix to Material + per-vertex colors and transparency
2016-02-17 Fix Bug #1545668 (Pcbnew can't open P-CAD ASCII files)
2016-02-18 Footprint generators in Python: add a rounding method to put a coordinate on a grid (PutOnGridMM and PutOnGridMils) .
2016-02-19 Make pin position and pin type columns sortable in dialog_lib_edit_pin_table.
2016-02-20 Remove CK1202_V1.pcb sample file, actually not used in Kicad, due to its unclear copyright. The http link to this sample file is in files.txt.
2016-02-21 Flush model data upon exit of Footprint Properties dialogs
2016-02-22 Added support for VRML2 Inline{}
2016-02-22 Pcbnew: fix a crash when trying to export a footprint in a non writable directory, or if a non writable old file was existing. (Linux only. On Windows, the wxWidgets file dialog dectects this issue)
2016-02-23 Revert accidental change to VRML logging levels
2016-02-23 Changed IDF plugin debug log from stderr to wxLogTrace
2016-02-23 Switched SG* classes and plugin loader logging code from stderr to wxLogTrace
2016-02-24 Python interface: add methods to add or remove layers to/from a layer set. Usefull to modify the layer set of pads Very minor other fixes.
2016-02-24 Remove outdated svg file.
2016-02-24 Remove wxASSERT in new cbbox code which was a nuisance to the legacy 3DViewer
2016-02-25 fix build error after Fix issues in PCAD import of P-CAD ASCII files in bzr6583-production
2016-02-25 CvPcb, filtering fp list by wildcard: Remove dialog to enter the filtering pattern. Use a wxTextCtrl permanently shown in toolbar. The fplist is updated immediately after editing the pattern.
2016-02-26 Changed resolver failure message to use wxLogMessage instead of wxMessageBox
2016-02-26 GOST-doc-gen: enhanced searching for Open/LibreOffice
2016-02-28 Remove redundant file
    Function is provided by events_called_functions.cpp
2016-02-29 add internat RU kicad.po file
2016-02-29 Fix compilation and install for OSX plus general code cleanup
2016-03-01 Fix character encoding of two source files
    These had quotes and dashes from Windows-1252, replaced with ASCII
2016-03-01 Added comments to 3D Plugin CMake files regarding debugging output
2016-03-02 update Russian GUI translate
2016-03-04 Pcbnew, File menu: break Open (board) into 2 menu items: Open (only for Kicad board files) and Import (only for non Kicad board files)
2016-03-06 Eeschema: SCH_SHEET_LIST improvements.
    * Derive SCH_SHEET_LIST from std::vector rather than using internal array
    management. Change all internal code to use iterators or array operator
    in loops.
    * Allow creation of empty SCH_SHEET_LIST for external population for plotting
    and printing.
    * Clean up print an plot code to take advantage of new SCH_SHEET_LIST behavior.
2016-03-08 pcbnew: remove dead legacy save code
2016-03-11 Documentation: add missing dependency to compiling with msys2.
2016-03-13 pcbnew: fix exception when import pcad pcb with zero size pads: zero size pads are now just ignored.
2016-03-14 MinGW64 build warning fixes.
    * On MinGW64 and possibly other 64-bit platforms, time_t is defined as a long
    long unsigned integer but all of the scanf and printf format specifiers used
    to save and load the schematic files are %lX which is a long unsigned integer
    which causes compile warnings. Add casts and temporary variables to eliminate
    the compile type warnings.
2016-03-15 Eeschema: fix a stupid bug which prevents the netlister to output the right pin electrical type in netlist.
2016-03-17 update translate Russian GUI
2016-03-18 pcbnew: fix Duplicate assertion in legacy also (lp:1558913)
    Do not assert that the item to be duplicated can be duplicated, just don't
    duplicate it. The user can trigger a Duplicate on items that aren't
    duplicatable, like field texts - he'll figure out that they can't be duplicated
    when they aren't, no need to deliver a scary warning and risk an abort.
2016-03-20 Change misspelled dxf conversion constant from member variable to static const like other conversion constants
2016-03-20 Remove a change which was committed by accident in rev 6632
2016-03-21 fix translate Russian GUI
2016-03-21 Enable C++11 support.
2016-03-22 fix page_layout_default_description (missing parenthesis before the keyword "end" in a few lines)
2016-03-22 Pcbnew: prevent zone tool from switching to no tool when deleting zone corner.
2016-03-23 eeschema: Remove incorrect assert on Edit with Library Editor
2016-03-23 Rework on class EDA_TEXT and related classes and draw functions. More work. Eechema: in rotate texts: redraw the full screen to avoid garbage on screen.
2016-03-26 GOST-doc-gen: partially updated odfpy integration code
2016-03-29 Hotkeys Editor has now a "reset to default" button
2016-03-30 eeschema: fix component search result ranking
2016-03-30 eeschema: fix create BOM-old variant
2016-03-31 gost: fix new SCH_SHEEL_LIST improvements
2016-04-03 Removed incorrect special treatment of commas within VRML files
2016-04-04 Eeschema: fix field edit dialog power component warning bug.
    * Prevent power component warning from being shown when edit normal component
    fields.
    * Make text edit dialog size itself instead of using a fixed size.
    * Improve the alignment and spacing in the text edit dialog.
2016-04-06 fix translateRussian GUI, 10-x hhg from electronix.ru/forum/kicad
2016-04-07 3D: fix bounding box assert and include order
2016-04-07 Fix a few Coverity warnings and typo is dialogs
2016-04-08 Eeschema: fix wxFileDialog assertion when importing component. (fixes lp:1558486)
    * wxFileDialog ctor was setting the file name using the most recently used
    path which was incorrect. Set the file path parameter to the most recently
    used path and the file name parameter to an empty string.
    * Remove last used import path and use the application wide most recently
    path instead.
    * Remove last used export path and use the application wide most recently
2016-04-09 Adjust spacing in dialog_edit_module_text
2016-04-10 dialog_edit_module_text: fix display bugs
    Displayed angle should be clamped to -90..90, 0 should not be displayed as
    blank text, and locale should be used for initial rendering.
2016-04-10 Clean up wxValidator window association
    wxValidator::SetWindow was used too many times due to me being a dunderhead who
    can't read the docs.
2016-04-12 Very minor changes: minor coding style fixes, and remove a few local shadowed variables (mainly local variables having the same name in the same function) detected using " -Wshadow" gcc compil option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
2016-04-14 Gerber files: ensure the "level polarity dark" is set in each file (this is the default, but ensuring that is better and can avoid issues when panneling files)
2016-04-16 Very minor changes: remove a few local shadowed variables (mainly local variables having the same name in the same function) detected using " -Wshadow" gcc compil option ( No bug, just a better code 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
2016-04-17 3D file name resolver improvements.
    * Paths defined via pcbnew->Preferences->Configure Paths are now included in
    the 3D file browser's drop-down list except for KICAD_PTEMPLATES, KIGITHUB,
    KISYSMOD, any paths resembling a URL, and any non-existent paths. When an
    absolute path is shortened using one of these path aliases, let's say
    'KISYS3DMOD' then the name appears in the pcb file as "${KISYS3DMOD}/blah.wrl".
    If a user defines and actual environment variable with the same name, then
2016-05-18 pcad2kicad: fixed an issue with an uppercase fileUnits parameter
2016-06-07 pcbnew: picad2kicad - fix compile issue
2016-09-01 pcbnew: fix build issue in bitmaps.h
2016-10-04 add new files from git-repo
2016-11-27 add new files from production
2017-03-06 pcbnew: macros menu return to menu bar
2017-05-03 add forgotten files in bzr4447
2017-11-04 pcad2kicadsch: fix align of pins to default grid (50 mils). All sizes increased to factor 1.27
2017-11-04 Fix previous commit
2017-11-12 pcad2kicadsch: use valid orientation of RefDes and Value fields
    Fixes: lp:1730698
    * https://bugs.launchpad.net/kicad/+bug/1730698
2017-11-16 pcad2kicadsch: import of wire to bus entries
    Fixes: lp:1732519
    * https://bugs.launchpad.net/kicad/+bug/1732519
2017-11-18 pcad2kicadsch: fix power references (prepend the symbol #)
2017-11-19 pcad2kicadsch: fix import a height and a visibility name/num text of pins
2017-11-19 pcad2kicadsch: line default width 10 mils
2017-11-20 pcad2kicadsch: fix import rotation of text
2017-11-21 pcad2kicadsch: replace quotes in symbol name to '_' (Kicad doesn't support quotes in a symbol name)
2017-11-25 pcad2kicadsch: convert local labels to global (PCAD supports only global ports)
2017-11-25 pcad2kicadsch: individual for each pin a visibility name/number
2017-11-26 pcad2kicadsch: fix not connected Wire Labels
2017-12-02 pcad2kicadsch: import IEEE symbols
